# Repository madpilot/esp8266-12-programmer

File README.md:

# ESP8266-12 Programmer

## Bill of Materials

* 2 x SKPMAME010 - [ALPS Tactile Switches](https://www.aliexpress.com/item/Free-Shipping-10pcs-6-6-5mm-SMD-Tactile-Push-Button-Tact-Switch-Silent-Switch-for-PCB/32432378759.html)
* 8 x [PCB Mount Pogo Pins](https://www.aliexpress.com/item/3-0-14-2mm-male-spring-loaded-PCB-mount-pogo-pin-connector-for-electronic-products/32814651096.html)
* 3 x 3k3 0805 SMD Resistor
* 2 x 1uF 0805 SMD Capacitor
* 1 x LM1117-3.3 LDO
* 1 x 2x1 0.1" Pin Header
* 1 x 6x1 0.1" Pin Header
* 1 x 3x1 0.1" Pin Header
* 1 x 0.1" Jumper

View this project on [CADLAB.io](https://cadlab.io/node/854).

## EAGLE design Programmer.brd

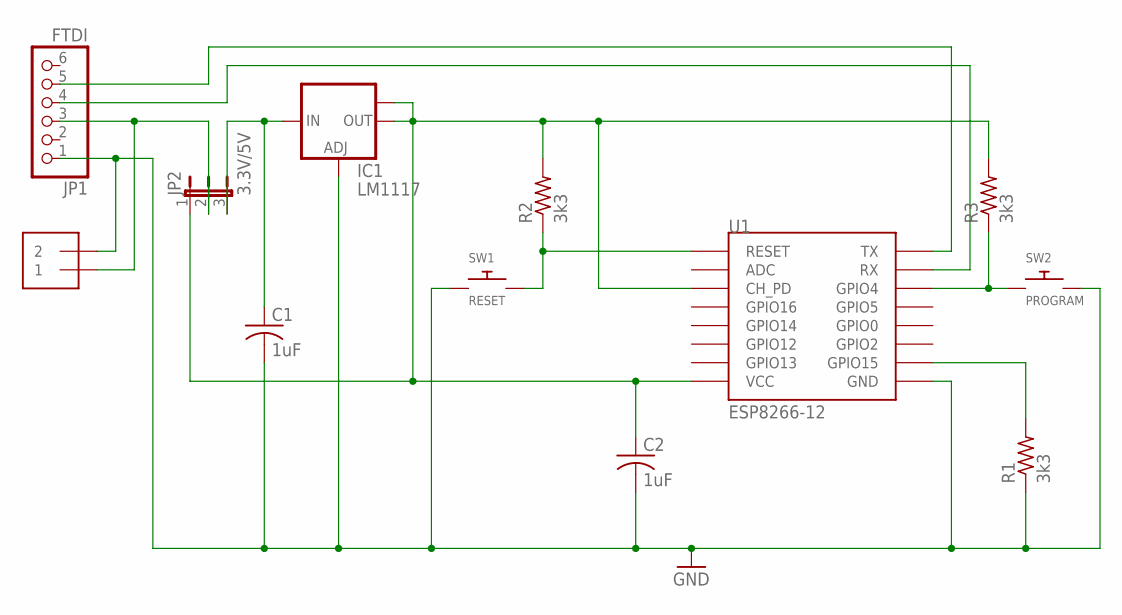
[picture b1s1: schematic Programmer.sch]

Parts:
C1, C2: 1uF; C0805
IC1: LM1117; SOT223
J1: 1X2; 1X02
JP1: FTDI; 1X06
JP2: 3.3V/5V; JP2
R1, R2, R3: 3k3; M0805
SW1: RESET; PUSHBUTTON_SMD_SJ
SW2: PROGRAM; PUSHBUTTON_SMD_SJ
U1: ESP8266-12; ESP12

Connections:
GND: C1.2, C2.2, IC1.1 (ADJ), J1.2, JP1.1, R1.1, SW1.P$1, SW2.P$2, U1.GND
unnamed: J1.1, JP1.3, JP2.2
unnamed: C1.1, IC1.3 (IN), JP2.3
unnamed: C2.1, IC1.2 (OUT), IC1.TAB (OUT1), JP2.1, R2.2, R3.2, U1.CH_PD, U1.VCC
unnamed: R2.1, SW1.P$2, U1.RESET
unnamed: R1.2, U1.GPIO15
unnamed: R3.1, SW2.P$1, U1.GPIO4
unnamed: JP1.5, U1.TX
unnamed: JP1.4, U1.RX

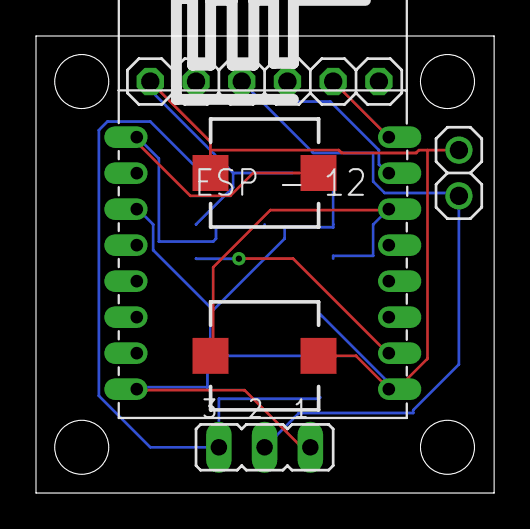
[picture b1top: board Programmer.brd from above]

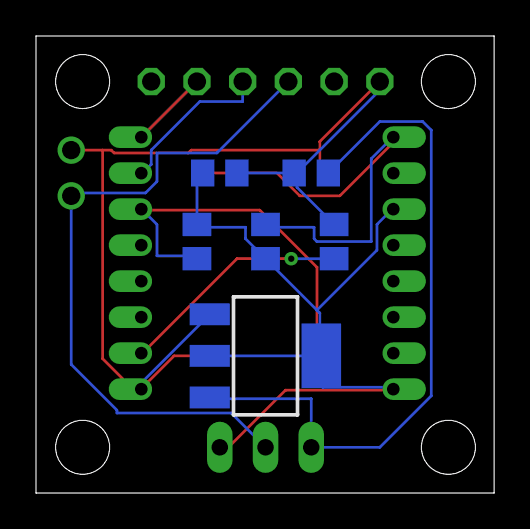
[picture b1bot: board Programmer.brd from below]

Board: 2 copper layers, 25.5 x 25.4 mm, 12 parts (6 on the bottom side), 9 nets.

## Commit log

2018-04-09 Initial Check in
2018-04-09 Backlink to CADLAB.io has been added.
2018-04-09 Adding BOMto README
2018-04-09 Formatting BOM
2018-04-09 addinf PCBWay compatible CAM file
